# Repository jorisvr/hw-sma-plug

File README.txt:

SMA2 Plug v2
  ============

The SMA2 Plug is a small printed circuit board (PCB) which can
be used as an extension module to attach coaxial cables to
an FPGA board.

One side of the module has two SMA connectors which can be used
either as digital input or as digital output at TTL level.
The other side of the module has a 2x6 pin header for plugging
into an FPGA board, compatible with the Digilent Pmod specification.

For more details, see the user manual
https://github.com/jorisvr/hw-sma-plug/blob/master/sma2_plug_v2/doc/manual.pdf

The SMA2 Plug is an open hardware design. This repository contains
the complete KiCad design files and design documents for the module.

  Acknowledgements
  ----------------

Many thanks to Sidney Cadot for fundamental ideas about features
and use cases for this module and detailed discussions on the design.

Many thanks to Joris van Zwieten for reviewing the design and
for invaluable advice on SMD soldering.

  License
  -------

Copyright 2020 Joris van Rantwijk

This design documentation describes Open Hardware and is licensed
under the CERN-OHL-S v2.

You may redistribute and modify this documentation and make products
using it under the terms of the CERN-OHL-S v2
(https://cern.ch/cern-ohl).

This documentation is distributed WITHOUT ANY EXPRESS OR IMPLIED
WARRANTY, INCLUDING OF MERCHANTABILITY, SATISFACTORY QUALITY AND
FITNESS FOR A PARTICULAR PURPOSE. Please see the CERN-OHL-S v2
for applicable conditions.

Source location: https://github.com/jorisvr/hw-sma-plug

--

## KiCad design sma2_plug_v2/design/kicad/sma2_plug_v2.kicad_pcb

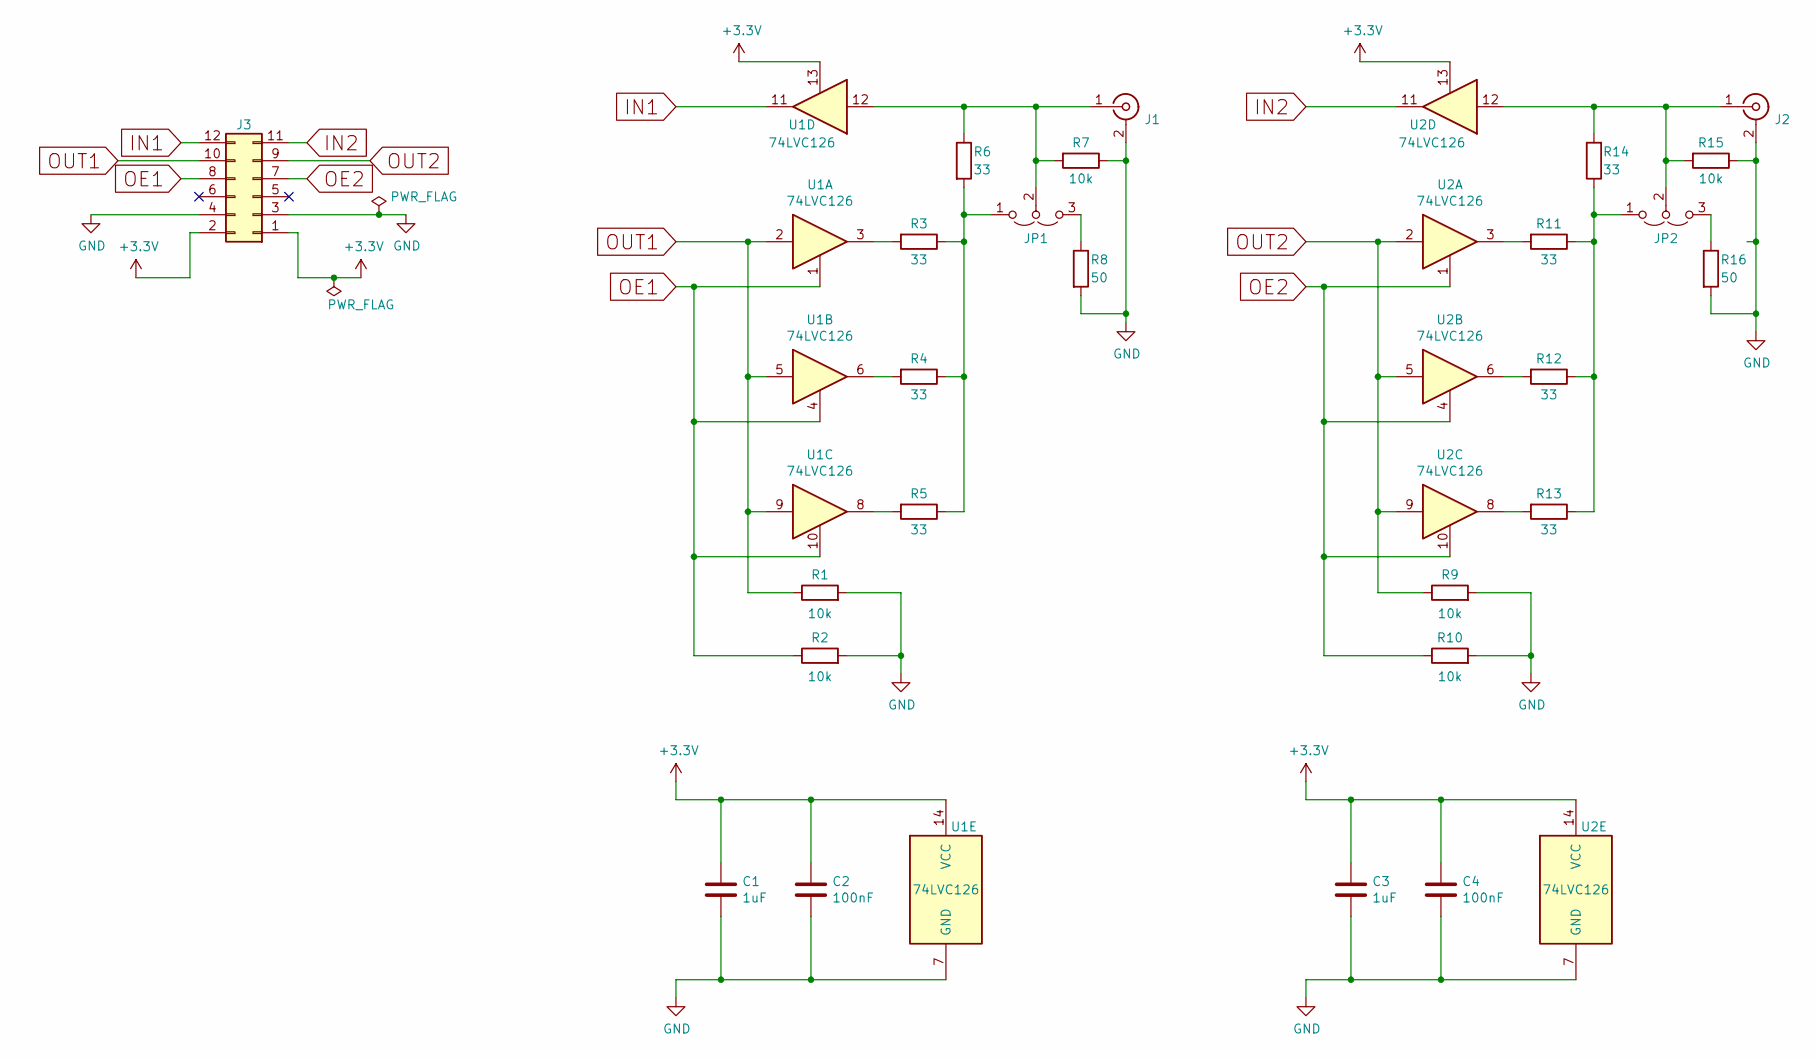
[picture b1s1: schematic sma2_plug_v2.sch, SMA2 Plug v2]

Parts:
C1, C3: 1uF; C_0805_2012Metric_Pad1.15x1.40mm_HandSolder
C2, C4: 100nF; C_0805_2012Metric_Pad1.15x1.40mm_HandSolder
J1, J2: Conn_Coaxial; SMA_Samtec_SMA-J-P-X-ST-EM1_EdgeMount
J3: Conn_02x06_Top_Bottom; PinHeader_2x06_P2.54mm_Horizontal
JP1, JP2: Jumper_3_Open; PinHeader_1x03_P2.54mm_Vertical
R1, R2, R7, R9, R10, R15: 10k; R_0805_2012Metric_Pad1.15x1.40mm_HandSolder
R3, R4, R5, R6, R11, R12, R13, R14: 33; R_0805_2012Metric_Pad1.15x1.40mm_HandSolder
R8, R16: 50; R_1206_3216Metric_Pad1.42x1.75mm_HandSolder
U1, U2: 74LVC126; SOIC-14_3.9x8.7mm_P1.27mm

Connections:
+3V3: C1.1, C2.1, C3.1, C4.1, J3.1, J3.2, U1.13, U1.14 (VCC), U2.13, U2.14 (VCC)
GND: C1.2, C2.2, C3.2, C4.2, J1.2 (Ext), J2.2 (Ext), J3.3, J3.4, R1.2, R2.2, R7.1, R8.2, R9.2, R10.2, R15.1, R16.2, U1.7 (GND), U2.7 (GND)
IN1: J3.12, U1.11
IN2: J3.11, U2.11
unnamed: J1.1 (In), JP1.2 (C), R6.1, R7.2, U1.12
unnamed: J2.1 (In), JP2.2 (C), R14.2, R15.2, U2.12
unnamed: JP1.1 (A), R3.1, R4.1, R5.1, R6.2
unnamed: JP1.3 (B), R8.1
unnamed: JP2.1 (A), R11.1, R12.1, R13.1, R14.1
unnamed: JP2.3 (B), R16.1
unnamed: R3.2, U1.3
unnamed: R4.2, U1.6
unnamed: R5.2, U1.8
unnamed: R11.2, U2.3
unnamed: R12.2, U2.6
unnamed: R13.2, U2.8
OE1: J3.8, R2.1, U1.1, U1.4, U1.10
OE2: J3.7, R10.1, U2.1, U2.4, U2.10
OUT1: J3.10, R1.1, U1.2, U1.5, U1.9
OUT2: J3.9, R9.1, U2.2, U2.5, U2.9

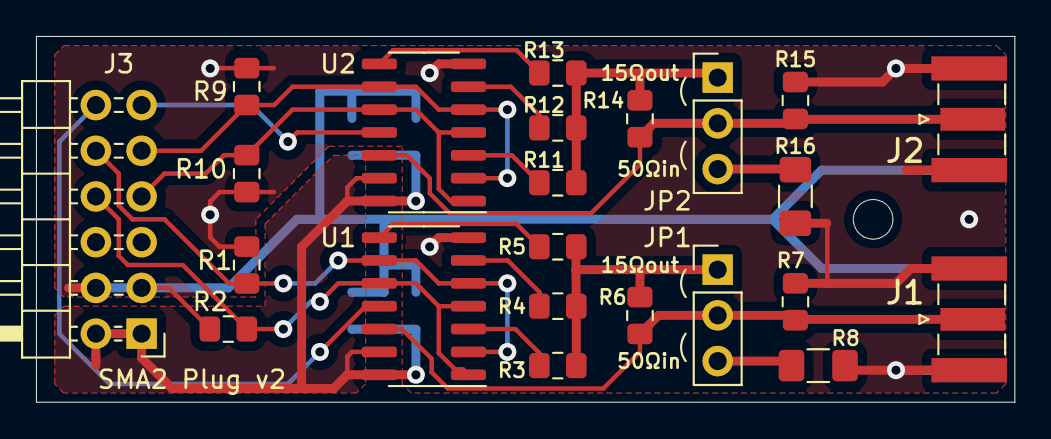
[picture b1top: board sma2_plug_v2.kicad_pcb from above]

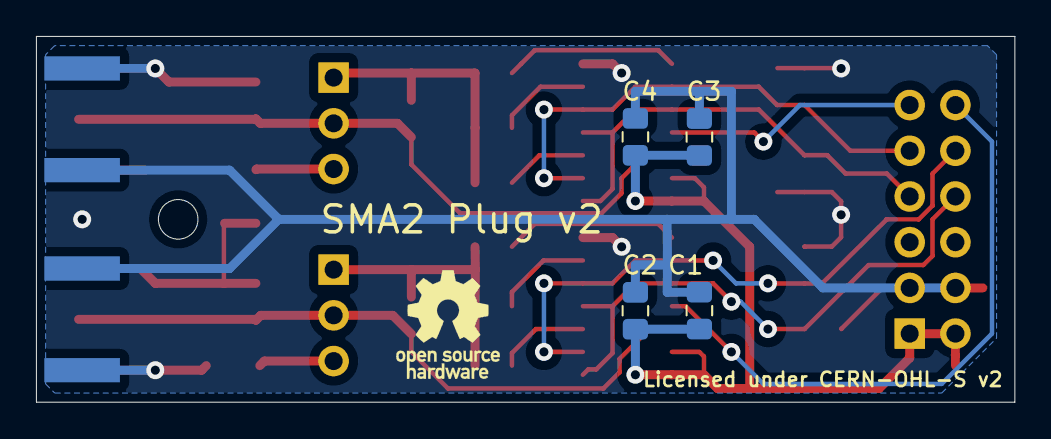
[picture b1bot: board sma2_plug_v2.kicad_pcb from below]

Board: 2 copper layers, 54.4 x 20.3 mm, 27 parts (4 on the bottom side), 20 nets.

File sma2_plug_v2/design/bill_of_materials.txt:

Bill of materials for SMA2 Plug v2
==================================

  qty  manufacturer + part nr          description                  package   Farnell  Conrad   refdes
  ---  ----------------------          -----------                  --------  -------  -------  ------
    2  Nexperia 74LVC126AD             quad logic buffer 74LVC126   SOIC-14   1631665           U1,U2
    2  KEMET C0805C105K3RAC            capacitor 1uF 25V X7R        0805      1637035  458056   C1,C3
    2  KEMET C0805C104J5RAC            capacitor 100nF 50V X7R      0805      1414663  458028   C2,C4
    6  Bourns CR0805-JW-103ELF         resistor 10 kOhm             0805      2008390  1055517  R1,R2,R7,R9,R10,R15
    8  Multicomp MP000066              resistor 33 Ohm 250 mW       0805      3127836           R3,R4,R5,R6,R11,R12,R13,R14
    2  Bourns CRM1206-FX-51R0ELF       resistor 51 Ohm 500 mW       1206      1865251           R8,R16
    2  Samtec SMA-J-P-H-ST-EM1         SMA connector edge-mount               2856818           J1,J2
    1  Wurth 61301221021               male pin header 2x6 angled   2.54rm    2356197  1898789  J3
    2                                  male pin header 1x3 straight 2.54rm    3226003  1581014  JP1,JP2
    2                                  jumper bridge 2.54rm                   2834673  1303885

NOTE: R8, R16 must be rated for at least 500 mW.
NOTE: R6, R14 must be rated for at least 250 mW.

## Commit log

2020-05-31 Add README and license
2020-07-24 Add design files and documents for SMA2 Plug v2
2020-07-24 Fix link in README

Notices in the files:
sma2_plug_v2/design/kicad/sma2_plug_v2.kicad_pcb:
Licensed under CERN-OHL-S v2, see also https://cern.ch/cern-ohl
sma2_plug_v2/design/kicad/sma2_plug_v2.sch:
Licensed under CERN-OHL-S v2 https://cern.ch/cern-ohl
